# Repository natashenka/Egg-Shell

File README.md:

Egg-Shell
=========

Tamagotchi Development Tools

See workshop.pdf for details on how to reprogram your Tamagotchi!

tASMgotchi uses the reliable exploit described in this issue, the other tools use intended functionality of the figure.

"makiko" is a clean figure image with no modifications that can be used to reproduce the exploit in the issue.

Have fun!

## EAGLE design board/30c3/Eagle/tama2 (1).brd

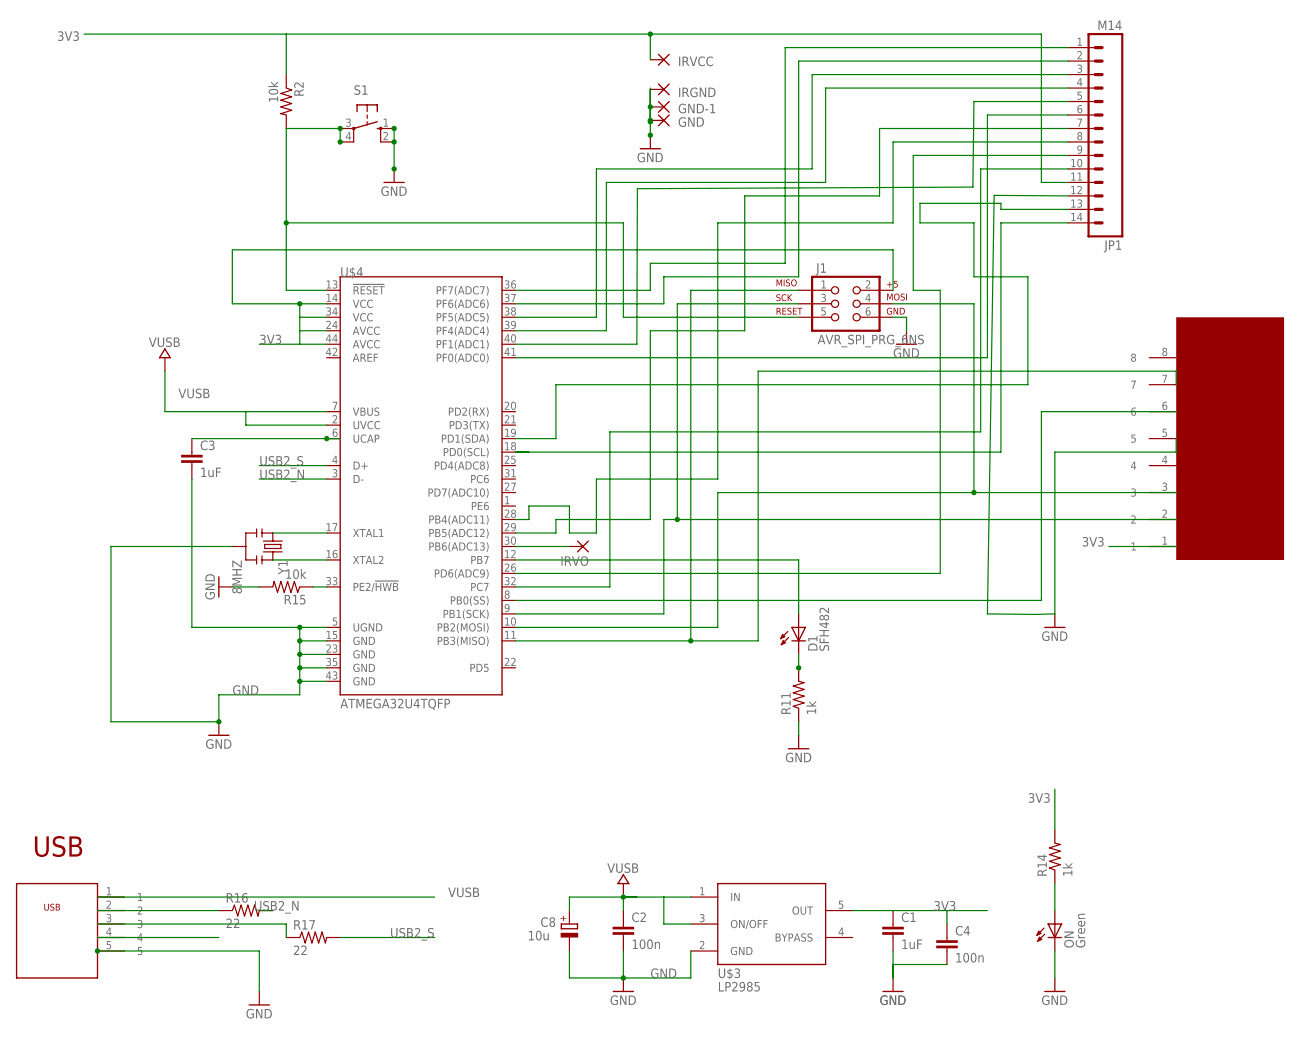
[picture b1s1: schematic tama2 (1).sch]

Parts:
C1, C3: 1uF; C1206
C2, C4: 100n; C1206
C8: 10u; SMC_B
D1: SFH482
GND: 2,15/1,0
GND-1: 2,15/1,0
IRGND: 2,15/1,0
IRVCC: 2,15/1,0
IRVO: 2,15/1,0
J1: AVR_SPI_PRG_6NS; 2X3-NS
JP1: M14; 1X14
ON: Green; CHIPLED_0805
R2, R15: 10k; R1206
R11, R14: 1k; R1206
R16, R17: 22; R1206
S1: 10-XX; B3F-10XX
U$1: TAMA; TAMACONTACT
U$2: USB
U$3: LP2985; SOT23-5
U$4: ATMEGA32U4TQFP; SPARKFUN-DIGITALIC_TQFP44
Y1: 8MHZ; RESONATOR-SMD

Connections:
3V3: C1.1, C4.1, IRVCC.1, J1.2, JP1.11, R2.1, R14.2, U$1.1, U$3.5 (OUT), U$4.14 (VCC), U$4.24 (AVCC), U$4.34 (VCC), U$4.44 (AVCC)
GND: C1.2, C2.2, C3.2, C4.2, C8.-, GND.1, GND-1.1, IRGND.1, J1.6, JP1.12, ON.C, R11.1, R15.2, S1.1 (S), S1.2 (S1), U$1.5, U$2.5, U$3.2 (GND), U$4.5 (UGND), U$4.15 (GND), U$4.23 (GND), U$4.35 (GND), U$4.43 (GND), Y1.2
unnamed: ON.A, R14.1
unnamed: D1.K (C), R11.2
unnamed: R15.1, U$4.33 (PE2/!HWB)
PB0: U$1.6, U$4.8 (PB0(SS))
PB1: J1.3, U$1.2, U$4.9 (PB1(SCK))
PB2: J1.4, U$1.3, U$4.10 (PB2(MOSI))
PB3: J1.1, U$1.7, U$4.11 (PB3(MISO))
PB4: JP1.8, U$4.28 (PB4(ADC11))
PB5: JP1.7, U$4.29 (PB5(ADC12))
PB6: IRVO.1, U$4.30 (PB6(ADC13))
PB7: D1.A, U$4.12 (PB7)
PC7: JP1.10, U$4.32 (PC7)
PD0: JP1.14, U$4.18 (PD0(SCL))
PD1: JP1.13, U$4.19 (PD1(SDA))
PD6: JP1.9, U$4.26 (PD6(ADC9))
PF0: JP1.6, U$4.41 (PF0(ADC0))
PF1: JP1.5, U$4.40 (PF1(ADC1))
PF4: JP1.4, U$4.39 (PF4(ADC4))
PF5: JP1.3, U$4.38 (PF5(ADC5))
PF6: JP1.2, U$4.37 (PF6(ADC6))
PF7: JP1.1, U$4.36 (PF7(ADC7))
RESET: J1.5, R2.2, S1.3, S1.4 (P1), U$4.13 (!RESET)
UCAP: C3.1, U$4.6 (UCAP)
USB2_N: R16.2, U$4.3 (D-)
USB2_S: R17.2, U$4.4 (D+)
USBID: U$2.4
USB_N: R16.1, U$2.2
USB_Q: R17.1, U$2.3
VUSB: C2.1, C8.+, U$2.1, U$3.1 (IN), U$3.3 (ON/OFF), U$4.2 (UVCC), U$4.7 (VBUS)
XTAL1: U$4.17 (XTAL1), Y1.1
XTAL2: U$4.16 (XTAL2), Y1.3

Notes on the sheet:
USB

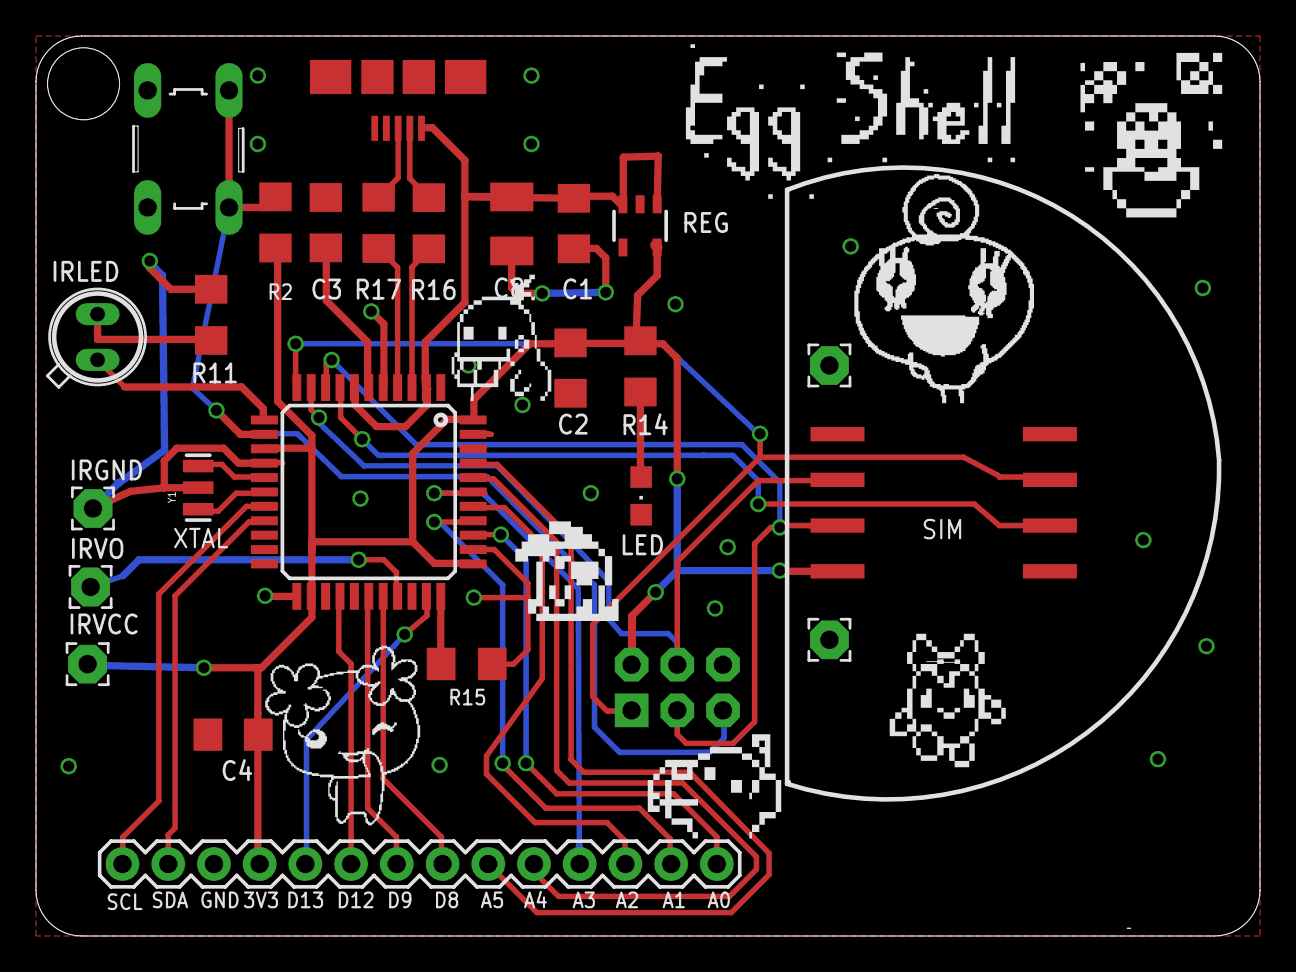
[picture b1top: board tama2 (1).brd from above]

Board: 4 copper layers, 68.0 x 50.0 mm, 26 parts (0 on the bottom side), 32 nets.

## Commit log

2013-09-08 Adding hardware info
2013-09-10 adding linux support
2013-09-10 adding windows
2013-09-10 tASMgotchi update
2013-09-10 typo
2013-09-12 slides
2013-09-14 update2
2013-11-08 Added an SMT crystal (not connected yet). Unsure if this is the right package...
2013-11-10 Redid the crystal based on the datasheet. (See pg 30 of the preliminary ATmega32U4 datasheet, doc7766.pdf)
2013-12-05 adding 30c3 edition
2013-12-05 de-mess-up-ifying
2013-12-24 Adding 30c3 slides
2013-12-29 Made itemmake working for all operating systems
2013-12-30 osx improvements
    Additions for error handling and debugging purposes. Modifications to
    make the script function better on slow serial-usb connections.
2014-01-03 Progress bar
2017-11-25 compatibility changes for Linux
2017-12-05 Improve 30c3 serw.py reliability
    Arduino Serial uses a fairly small buffer. Attempting to send 256 bytes
    at a time can easily overflow the buffer before it can be drained by the
    main loop and cause problems. By writing 16 bytes at a time, the buffer
    doesn't seem to overflow.
    While debugging this, I added checks that the write operations are
    actually completed by the flash chip. This removes the explicit delay()
2017-12-13 30c3 boardsw-v2: Fix write-in-progress polling
    Status register bit 0 is set to 1 while a write is in progress, not 0. Also
    change to a do/while to ensure the status register is read at least once.

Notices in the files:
parts and their libraries:
SparkFun-DigitalIC: Licensing: CC v3.0 Share-Alike You are welcome to use this library for commercial purposes.
